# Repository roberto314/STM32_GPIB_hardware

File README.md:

hardware for my STM32 IEEE488 to USB Converter.
firmware is here:

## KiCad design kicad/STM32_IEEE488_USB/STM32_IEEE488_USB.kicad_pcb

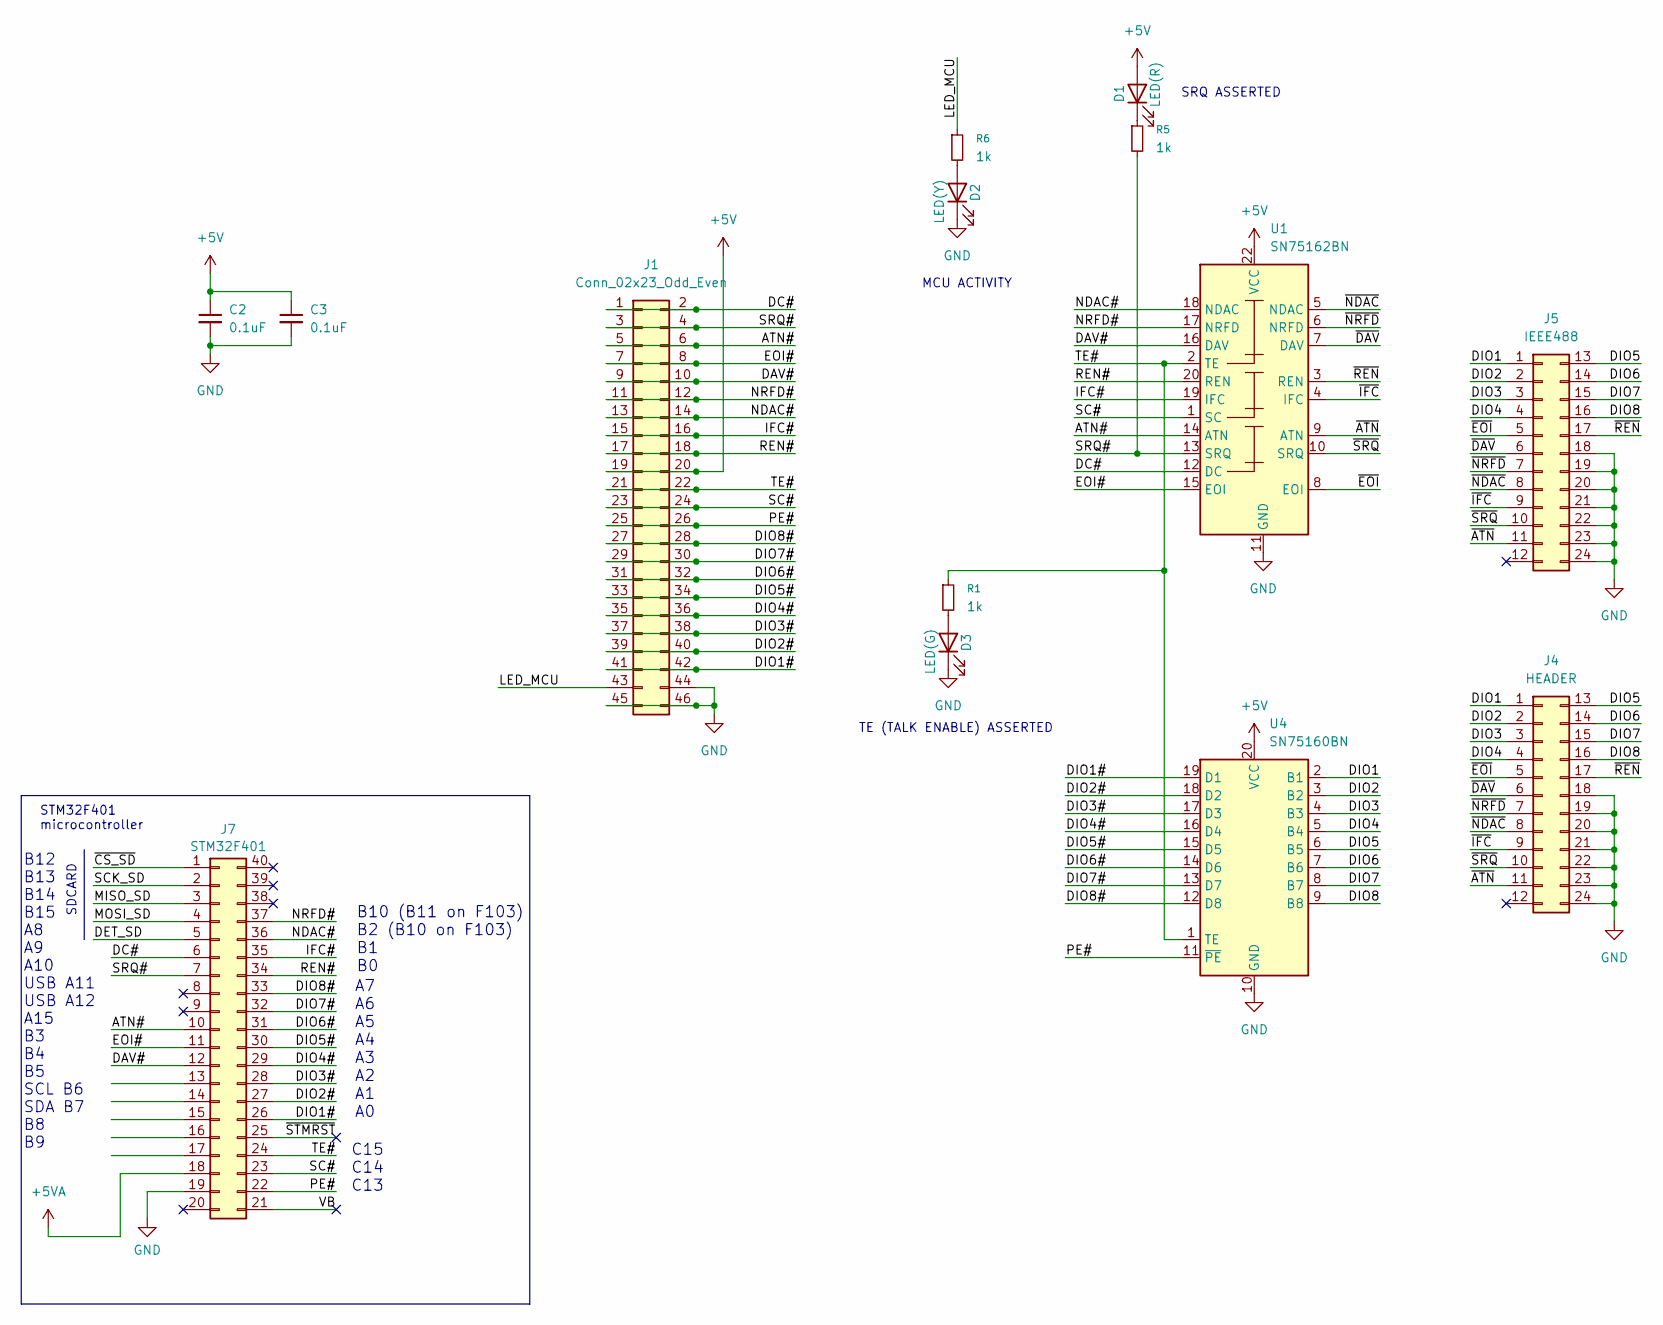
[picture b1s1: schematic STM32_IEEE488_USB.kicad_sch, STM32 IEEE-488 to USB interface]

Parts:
C2, C3: 0.1uF; C_Disc_D3.0mm_W1.6mm_P2.50mm; PartNo C320C104K5R5TA
D1: LED(R); LED_D5.0mm; PartNo LTL-307E
D2: LED(Y); LED_D5.0mm; PartNo LTL-307Y
D3: LED(G); LED_D5.0mm; PartNo LTL-307G
J1: Conn_02x23_Odd_Even; PinHeader_2x23_P2.54mm_Vertical
J4: HEADER; PinHeader_2x12_P2.54mm_Vertical
J5: IEEE488; IEEE488_horizontal_Pin1_near_edge; PartNo 112-024-113R001
J7: STM32F401; DIP-40_W15.24mm_Socket_LongPads
R1, R5, R6: 1k; R_1206_3216Metric_Pad1.30x1.75mm_HandSolder
U1: SN75162BN; DIP-22_W10.16mm_Socket; PartNo SN75162BN
U4: SN75160BN; DIP-20_W7.62mm; PartNo SN75160BN

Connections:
+5V: C2.1, C3.1, D1.2 (A), J1.19, J1.20, U1.22 (VCC), U4.20 (VCC)
/ATN#: J1.5, J1.6, J7.10, U1.14 (ATN)
/DAV#: J1.9, J1.10, J7.12, U1.16 (DAV)
/DC#: J1.1, J1.2, J7.6, U1.12 (DC)
/DIO1: J4.1, J5.1, U4.2 (B1)
/DIO1#: J1.41, J1.42, J7.26, U4.19 (D1)
/DIO2: J4.2, J5.2, U4.3 (B2)
/DIO2#: J1.39, J1.40, J7.27, U4.18 (D2)
/DIO3: J4.3, J5.3, U4.4 (B3)
/DIO3#: J1.37, J1.38, J7.28, U4.17 (D3)
/DIO4: J4.4, J5.4, U4.5 (B4)
/DIO4#: J1.35, J1.36, J7.29, U4.16 (D4)
/DIO5: J4.13, J5.13, U4.6 (B5)
/DIO5#: J1.33, J1.34, J7.30, U4.15 (D5)
/DIO6: J4.14, J5.14, U4.7 (B6)
/DIO6#: J1.31, J1.32, J7.31, U4.14 (D6)
/DIO7: J4.15, J5.15, U4.8 (B7)
/DIO7#: J1.29, J1.30, J7.32, U4.13 (D7)
/DIO8: J4.16, J5.16, U4.9 (B8)
/DIO8#: J1.27, J1.28, J7.33, U4.12 (D8)
/EOI#: J1.7, J1.8, J7.11, U1.15 (EOI)
/IFC#: J1.15, J1.16, J7.35, U1.19 (IFC)
/LED_MCU: J1.43, R6.1
/NDAC#: J1.13, J1.14, J7.36, U1.18 (NDAC)
/NRFD#: J1.11, J1.12, J7.37, U1.17 (NRFD)
/PE#: J1.25, J1.26, J7.22, U4.11 (~PE)
/REN#: J1.17, J1.18, J7.34, U1.20 (REN)
/SC#: J1.23, J1.24, J7.23, U1.1 (SC)
/SRQ#: J1.3, J1.4, J7.7, R5.2, U1.13 (SRQ)
/TE#: J1.21, J1.22, J7.24, R1.1, U1.2 (TE), U4.1 (TE)
/~ATN: J4.11, J5.11, U1.9 (ATN)
/~DAV: J4.6, J5.6, U1.7 (DAV)
/~EOI: J4.5, J5.5, U1.8 (EOI)
/~IFC: J4.9, J5.9, U1.4 (IFC)
/~NDAC: J4.8, J5.8, U1.5 (NDAC)
/~NRFD: J4.7, J5.7, U1.6 (NRFD)
/~REN: J4.17, J5.17, U1.3 (REN)
/~SRQ: J4.10, J5.10, U1.10 (SRQ)
GND: C2.2, C3.2, D2.1 (K), D3.1 (K), J1.44, J1.45, J1.46, J4.18, J4.19, J4.20, J4.21, J4.22, J4.23, J4.24, J5.18, J5.19, J5.20, J5.21, J5.22, J5.23, J5.24, J7.19, U1.11 (GND), U4.10 (GND)
unnamed: D1.1 (K), R5.1
unnamed: D2.2 (A), R6.2
unnamed: D3.2 (A), R1.2

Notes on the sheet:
SRQ ASSERTED
B12 B13 B14 B15 A8 A9 A10 USB A11 USB A12 A15 B3 B4 B5 SCL B6 SDA B7 B8 B9
SDCARD
STM32F401 microcontroller
A7 A6 A5 A4 A3 A2 A1 A0
B10 (B11 on F103) B2 (B10 on F103) B1 B0
C15 C14 C13
TE (TALK ENABLE) ASSERTED
MCU ACTIVITY

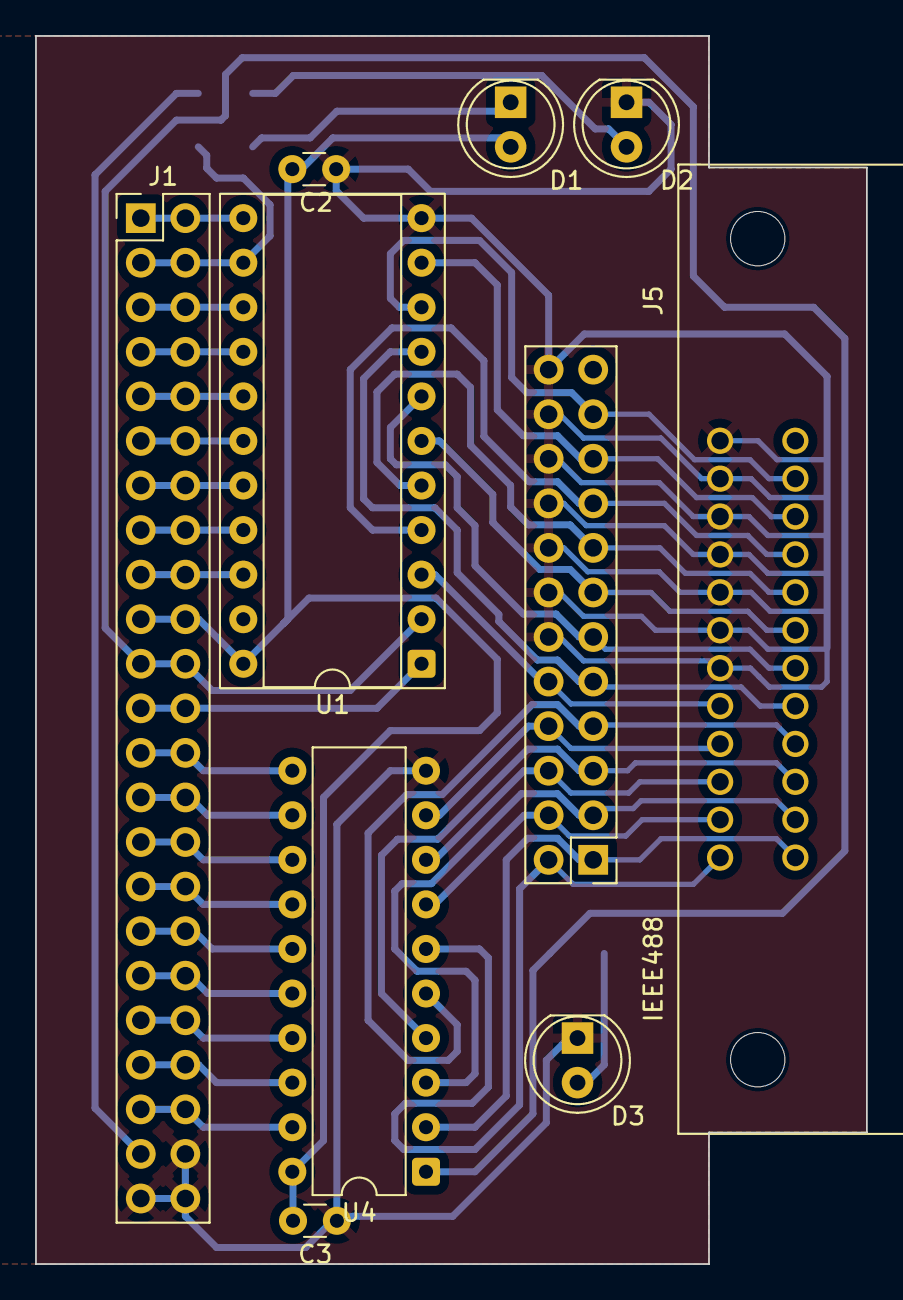
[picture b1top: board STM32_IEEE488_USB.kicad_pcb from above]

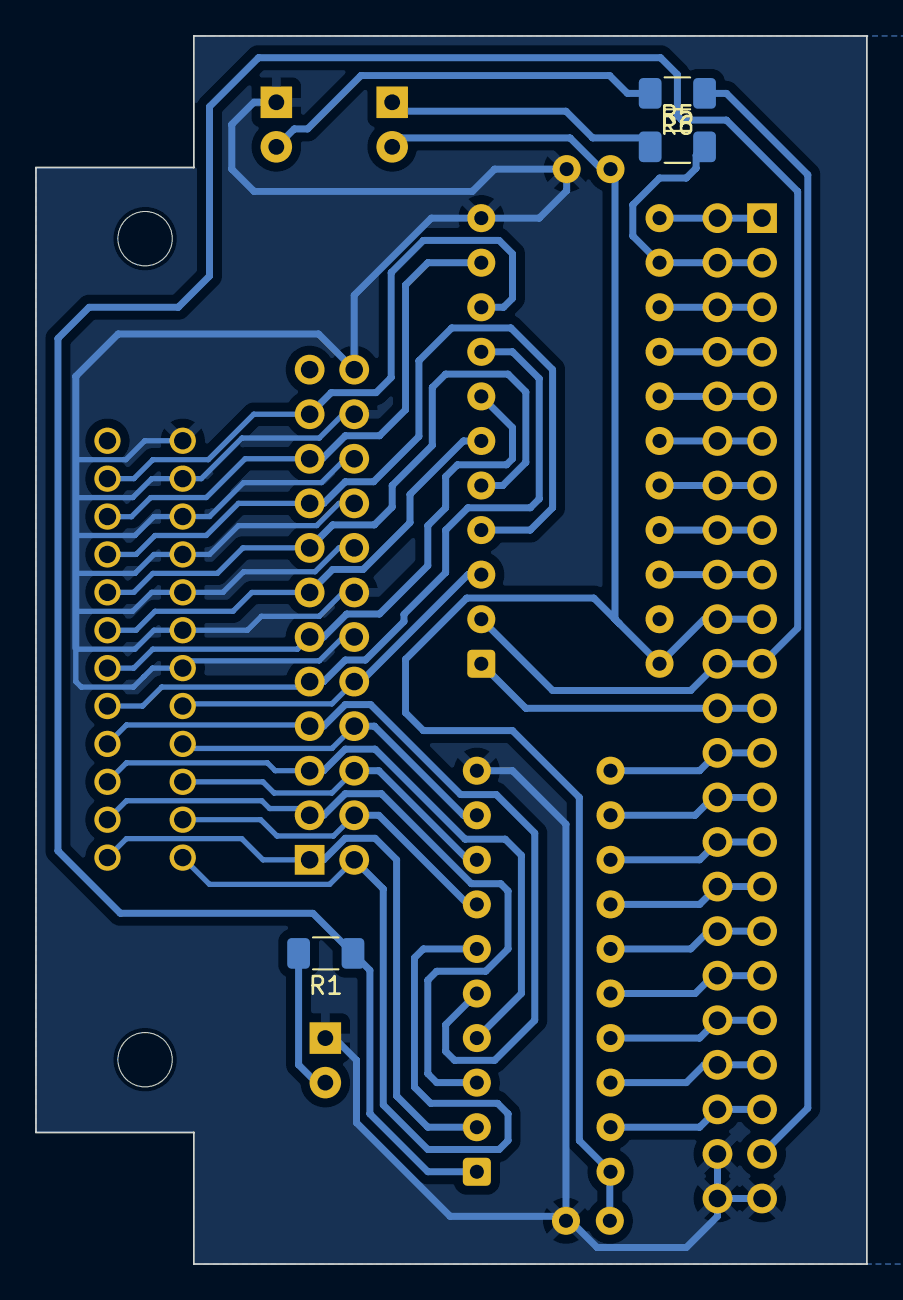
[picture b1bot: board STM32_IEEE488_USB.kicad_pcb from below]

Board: 2 copper layers, 47.4 x 70.0 mm, 13 parts (3 on the bottom side), 42 nets.

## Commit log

2026-03-05 initial
2026-03-05 Create README.md
    Readme added
2026-03-05 pinout fixed
2026-03-08 final pin arrangement
